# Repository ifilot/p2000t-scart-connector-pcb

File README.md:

# P2000T SCART adapter plate

Small four-layer PCB to interface the six wires of the RGBS port with a 
SCART connector.

## Purpose

To interface a P2000T with a SCART-compatible monitor or television, a couple
of resistors need to be placed. This PCB accommodates the resistors in a small
0805 form factor and allows for a sturdy connection with the SCART connector.

> **Warning**
> The SCART interface requires a **non-inverted** SYNC signal from the P2000T. Whether
> your P2000T outputs an inverted or non-inverted SYNC signal can be controlled
> by means of placing a solder joint on the mainboard of your P2000T. For more
> information, please consult [this website](https://www.philips-p2000t.nl/hardware/videoport.html#regular-or-inverted-sync-signal).

## PCBs

## Cable assembly

1. Solder the 0805 resistors onto the PCB.
2. Solder the wires onto the PCB and in turn solder the PCB to the SCART connector.
3. Place the SCART connector into its enclosure and close it.
4. Connect the wires to their corresponding terminals in the DIN6 connector.

The signals on the RBGS, as seen by looking into the female socket on the back
side of the P2000T, is provided below. **Note that the colors in the image below
do not necessarily correspond to the wire colors as shown above.**

In the image below, a P2000T is connected to a modern flat-screen television
with a SCART interface. As can be seen, the video quality is fairly good.
Note that different televisions use different soft- and hardware implementations
to convert the analog SCART signals to an image. The quality on your television
or monitor may vary.

## Bill of materials

* 2 x 2.2kΩ 0805 resistors
* 3 x 150Ω 0805 resistors
* 1 x 560Ω 0805 resistor
* 1 x SCART connector
* 1 x DIN6 male connector
* 6-wire cable

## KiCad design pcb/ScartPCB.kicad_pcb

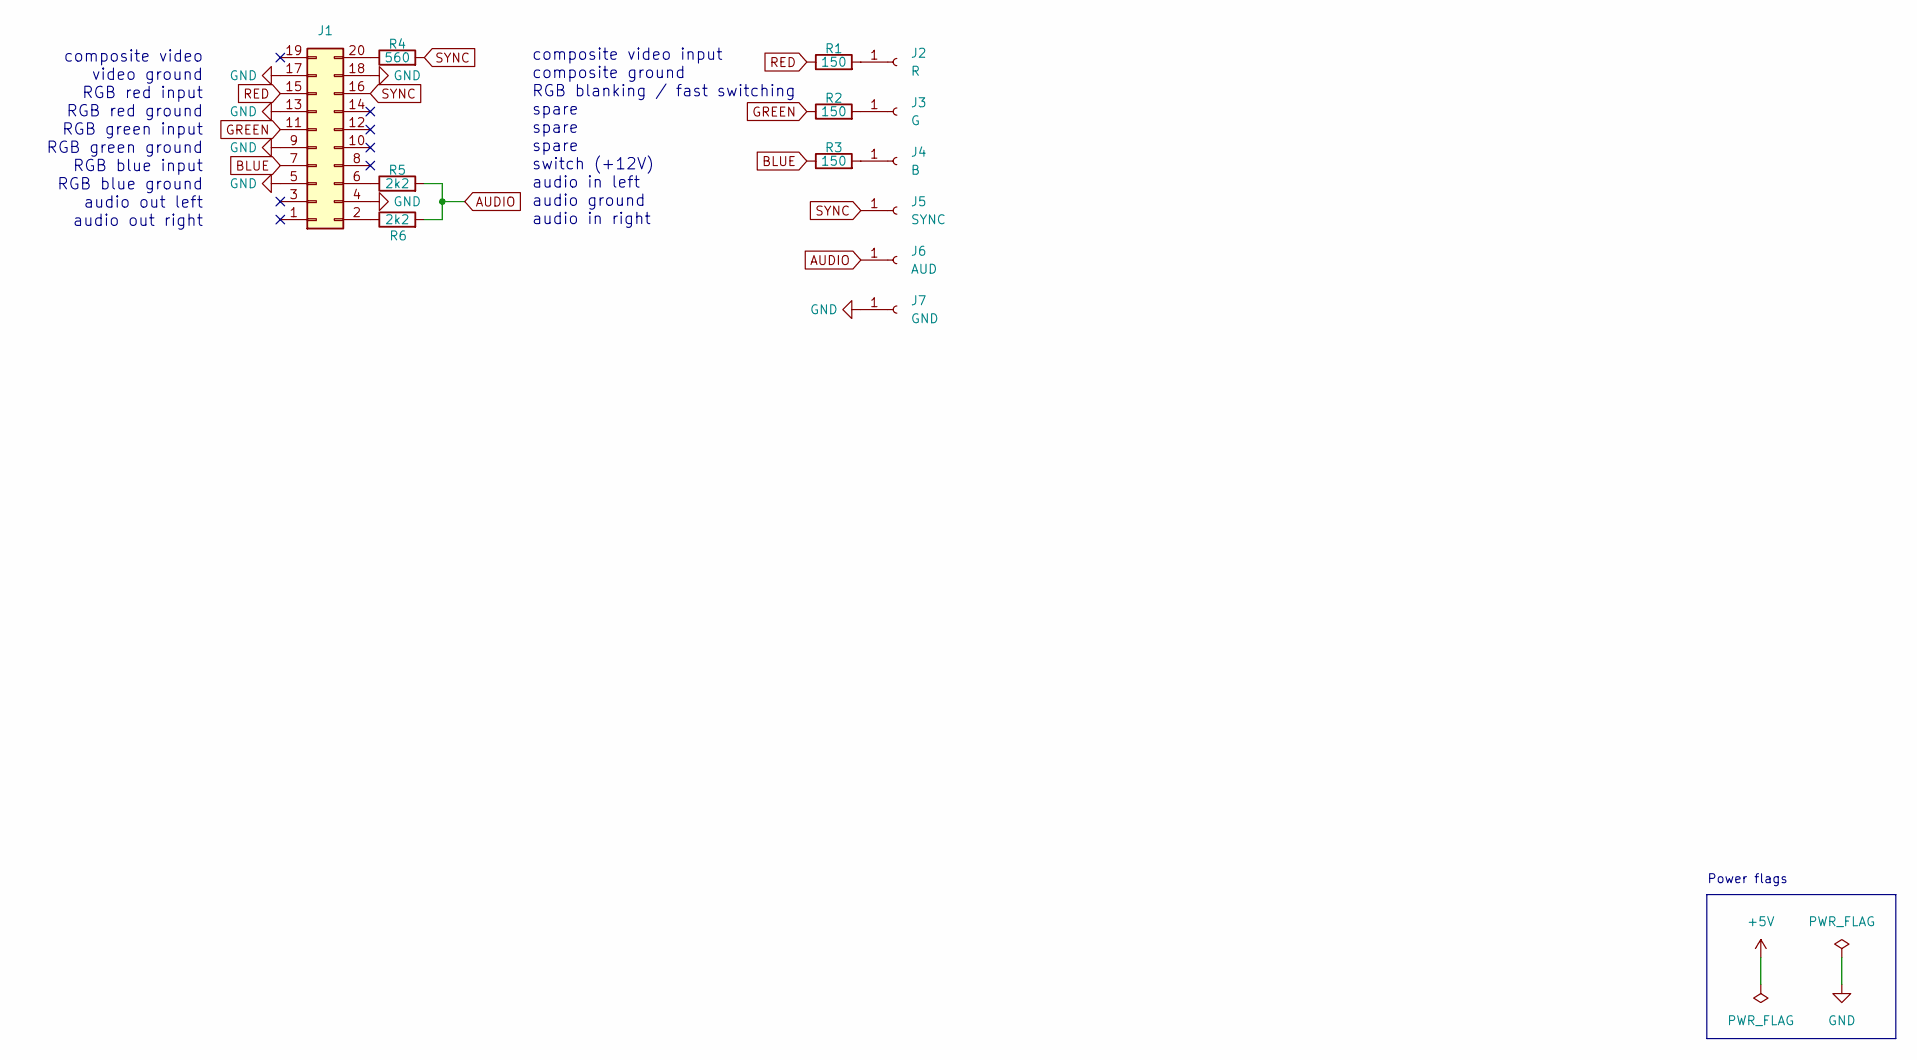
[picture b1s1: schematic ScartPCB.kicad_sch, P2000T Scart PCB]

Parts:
J1: Conn_02x10_Odd_Even; SCART
J2: R; SolderWire-0.75sqmm_1x01_D1.25mm_OD3.5mm
J3: G; SolderWire-0.75sqmm_1x01_D1.25mm_OD3.5mm
J4: B; SolderWire-0.75sqmm_1x01_D1.25mm_OD3.5mm
J5: SYNC; SolderWire-0.75sqmm_1x01_D1.25mm_OD3.5mm
J6: AUD; SolderWire-0.75sqmm_1x01_D1.25mm_OD3.5mm
J7: GND; SolderWire-0.75sqmm_1x01_D1.25mm_OD3.5mm
R1, R2, R3: 150; LED_0805_2012Metric_Pad1.15x1.40mm_HandSolder
R4: 560; LED_0805_2012Metric_Pad1.15x1.40mm_HandSolder
R5, R6: 2k2; LED_0805_2012Metric_Pad1.15x1.40mm_HandSolder

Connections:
AUDIO: J6.1, R5.2, R6.2
BLUE: J1.7, R3.1
GND: J1.4, J1.5, J1.9, J1.13, J1.17, J1.18, J7.1
GREEN: J1.11, R2.1
unnamed: J1.2, R6.1
unnamed: J1.6, R5.1
unnamed: J1.20, R4.1
unnamed: J2.1, R1.2
unnamed: J3.1, R2.2
unnamed: J4.1, R3.2
RED: J1.15, R1.1
SYNC: J1.16, J5.1, R4.2

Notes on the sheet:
Power flags
composite video input composite ground RGB blanking / fast switching spare spare spare switch (+12V) audio in left audio ground audio in right
composite video video ground RGB red input RGB red ground RGB green input RGB green ground RGB blue input RGB blue ground audio out left audio out right

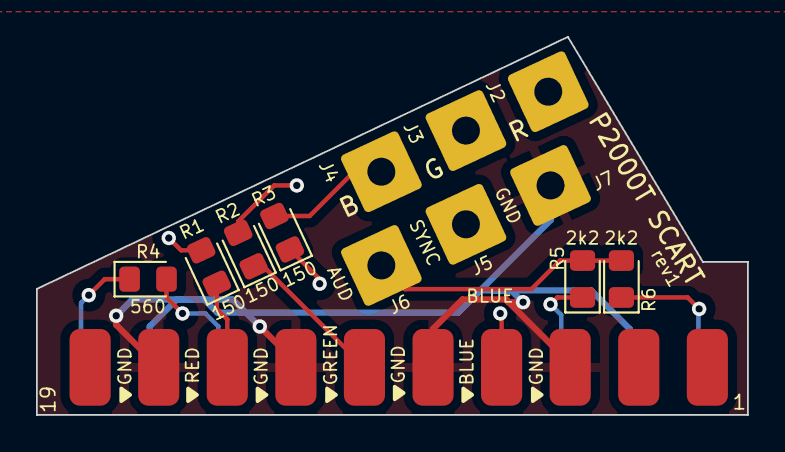
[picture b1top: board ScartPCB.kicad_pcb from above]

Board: 4 copper layers, 39.5 x 21.0 mm, 14 parts (1 on the bottom side), 12 nets.

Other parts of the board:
LOGO1: OSHW-Logo2_7.3x6mm_SilkScreen

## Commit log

2024-03-09 Revising PCB
2024-03-09 Adding images and README.md
2024-03-09 Expanding README.md
2024-03-09 Further expanding README.md
2025-10-17 Adding schematic PDF
